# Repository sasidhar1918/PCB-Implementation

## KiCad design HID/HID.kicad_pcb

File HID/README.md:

# RP2040 Custom HID Device: Technical Implementation

## 🚀 Project Overview
This project is a high-performance Human Interface Device (HID) built on the **Raspberry Pi RP2040** microcontroller. Moving beyond simple breadboard prototypes, this implementation features a production-ready PCB designed to handle high-speed USB data signals with professional-grade integrity.

---

## 🛠️ My Implementation Approach

### 1. High-Speed Data Integrity
For the USB-C interface, I prioritized signal quality for the **D+ and D- differential pairs**:
* **Routing:** Minimal trace length to reduce latency and interference.
* **Isolation:** Kept data lines isolated from noisy power components.
* **Grounding:** Implemented a robust ground system to provide a stable reference and prevent data corruption.

### 2. Thermal & Noise Management (Via Stitching)
A key technical feature of this design is the strategic use of **GND Via Stitching**:
* **Copper Pours:** Large planes on both Top and Bottom layers to eliminate "floating islands."
* **EMI Shielding:** Manual via placement creates a "Faraday cage" effect to suppress electrical noise.
* **Thermal Dissipation:** Efficiently transfers heat from the RP2040 into the bottom copper plane.

### 3. Power Delivery Architecture
Designed to handle 5V input from the USB-C receptacle with a focus on stability:
* **Filtering:** series of decoupling capacitors to suppress high-frequency noise.
* **Proximity:** Components placed as close as possible to the RP2040 power pins to handle sudden current draws from the dual-core processor.

### 4. Design for Excellence (DfX)
The layout adheres to strict **Design Rule Checks (DRC)** for seamless manufacturing:
* **Soldering:** Clearances optimized for easy component assembly.
* **Legibility:** Silkscreen labels are positioned to avoid overlap with solder pads.
* **CNC Ready:** Precisely defined board edges for factory routing.

---

## 📊 Technical Specifications

| Feature | Specification |
| :--- | :--- |
| **Core** | RP2040 (Dual ARM Cortex-M0+ @ 133MHz) |
| **Interface** | USB 2.0 via USB-C |
| **PCB Topology** | 2-Layer FR-4, 1.6mm thickness |
| **Grounding** | Symmetrical Top/Bottom copper pours with via stitching |

---

## 📂 How to Use This Project
This repository contains the full design source. You can explore the implementation details within the **KiCad files**, where I have documented:
* Specific trace widths.
* Clearance constraints used to achieve a **zero-error DRC report**.

---
*Designed and implemented with a focus on signal integrity and professional PCB manufacturing standards.*

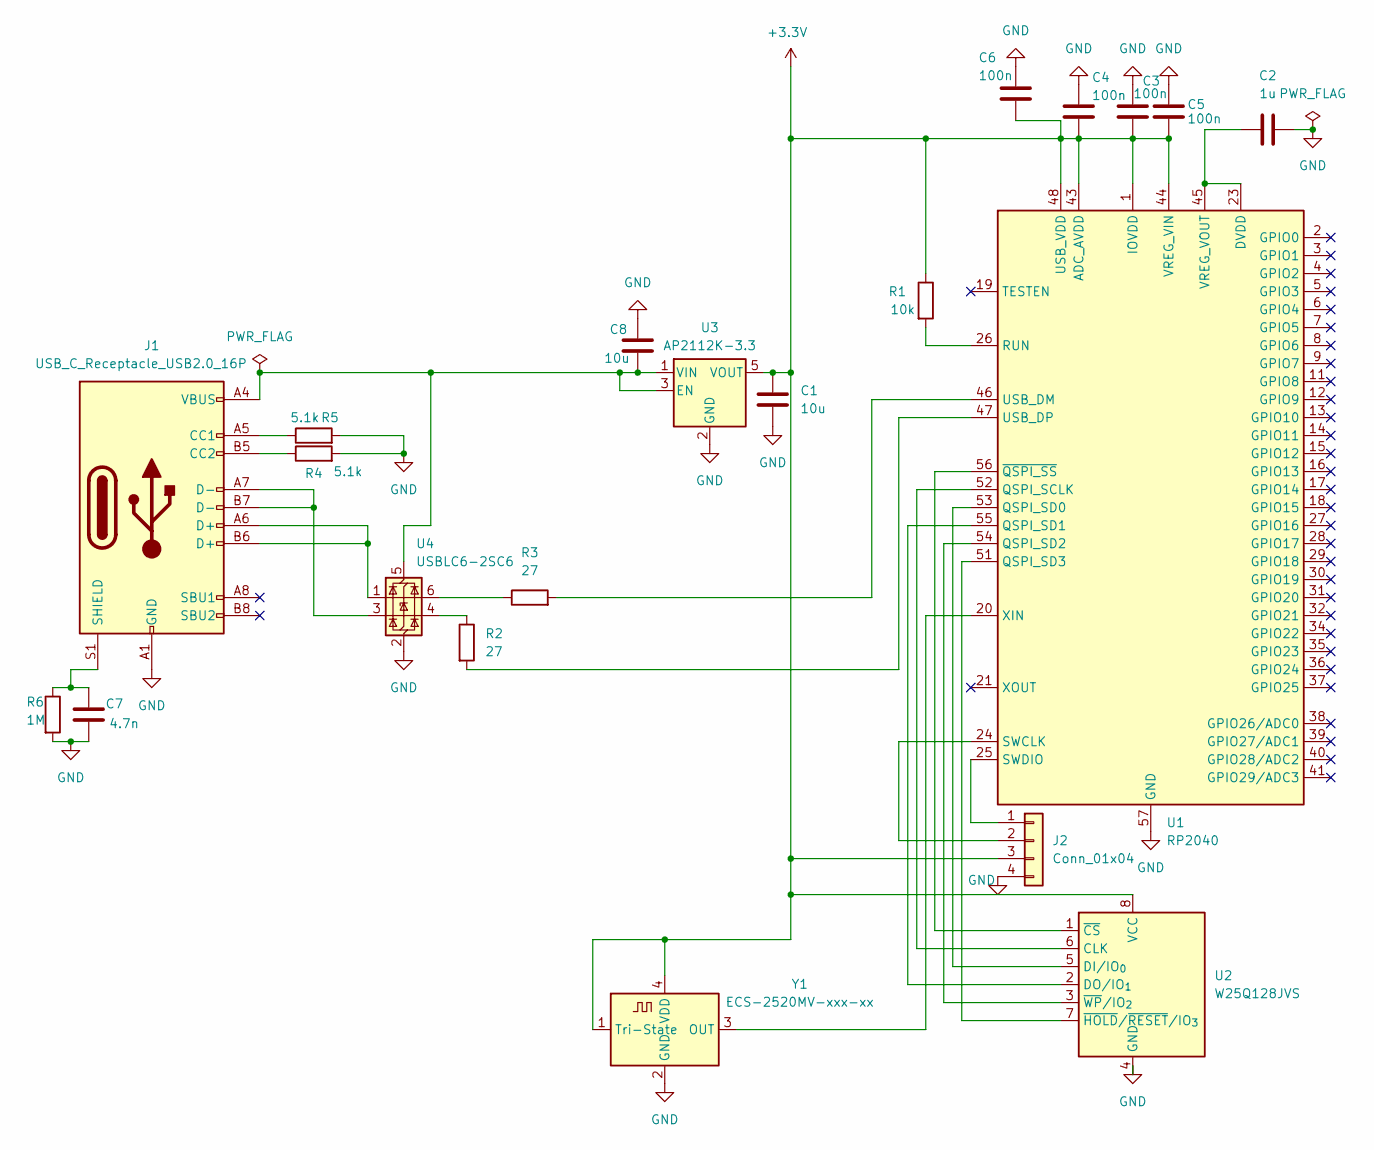
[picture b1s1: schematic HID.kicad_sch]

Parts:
C1, C8: 10u; C_0805_2012Metric_Pad1.18x1.45mm_HandSolder
C2: 1u; C_0805_2012Metric_Pad1.18x1.45mm_HandSolder
C3, C4, C5, C6: 100n; C_0805_2012Metric_Pad1.18x1.45mm_HandSolder
C7: 4.7n; C_0805_2012Metric_Pad1.18x1.45mm_HandSolder
J1: USB_C_Receptacle_USB2.0_16P; USB_C_Receptacle_GCT_USB4110
J2: Conn_01x04; PinHeader_1x04_P1.27mm_Vertical
R1: 10k; R_0805_2012Metric_Pad1.20x1.40mm_HandSolder
R2, R3: 27; R_0805_2012Metric_Pad1.20x1.40mm_HandSolder
R4, R5: 5.1k; R_0805_2012Metric_Pad1.20x1.40mm_HandSolder
R6: 1M; R_0805_2012Metric_Pad1.20x1.40mm_HandSolder
U1: RP2040; QFN-56-1EP_7x7mm_P0.4mm_EP3.2x3.2mm
U2: W25Q128JVS; SOIC-8_5.3x5.3mm_P1.27mm
U3: AP2112K-3.3; SOT-23-5
U4: USBLC6-2SC6; SOT-23-6
Y1: ECS-2520MV-xxx-xx; Oscillator_SMD_ECS_2520MV-xxx-xx-4Pin_2.5x2.0mm

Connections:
+3.3V: C1.1, C3.2, C4.2, C5.2, C6.2, J2.3, R1.1, U1.1 (IOVDD), U1.10 (IOVDD), U1.22 (IOVDD), U1.33 (IOVDD), U1.42 (IOVDD), U1.43 (ADC_AVDD), U1.44 (VREG_VIN), U1.48 (USB_VDD), U1.49 (IOVDD), U2.8 (VCC), U3.5 (VOUT), Y1.1 (Tri-State), Y1.4 (VDD)
GND: C1.2, C2.2, C3.1, C4.1, C5.1, C6.1, C7.2, C8.1, J1.A1 (GND), J1.A12 (GND), J1.B1 (GND), J1.B12 (GND), J2.4, R4.2, R5.2, R6.2, U1.57 (GND), U2.4 (GND), U3.2 (GND), U4.2 (GND), Y1.2 (GND)
unnamed: J1.A5 (CC1), R5.1
unnamed: J1.B5 (CC2), R4.1
unnamed: J1.A6 (D+), J1.B6 (D+), U4.1 (I/O1)
unnamed: J1.A7 (D-), J1.B7 (D-), U4.3 (I/O2)
unnamed: C7.1, J1.S1 (SHIELD), R6.1
unnamed: J2.1, U1.25 (SWDIO)
unnamed: J2.2, U1.24 (SWCLK)
unnamed: R2.1, U4.4 (I/O2)
unnamed: R3.1, U4.6 (I/O1)
unnamed: U1.52 (QSPI_SCLK), U2.6 (CLK)
unnamed: U1.53 (QSPI_SD0), U2.5 (DI/IO_{0})
unnamed: U1.55 (QSPI_SD1), U2.2 (DO/IO_{1})
unnamed: U1.54 (QSPI_SD2), U2.3 (~WP/IO_{2})
unnamed: U1.51 (QSPI_SD3), U2.7 (~HOLD/~RESET/IO_{3})
unnamed: R1.2, U1.26 (RUN)
unnamed: R3.2, U1.46 (USB_DM)
unnamed: R2.2, U1.47 (USB_DP)
unnamed: C2.1, U1.23 (DVDD), U1.45 (VREG_VOUT), U1.50 (DVDD)
unnamed: U1.20 (XIN), Y1.3 (OUT)
unnamed: U1.56 (~QSPI_SS), U2.1 (~CS)
unnamed: C8.2, J1.A4 (VBUS), J1.A9 (VBUS), J1.B4 (VBUS), J1.B9 (VBUS), U3.1 (VIN), U3.3 (EN), U4.5 (VBUS)

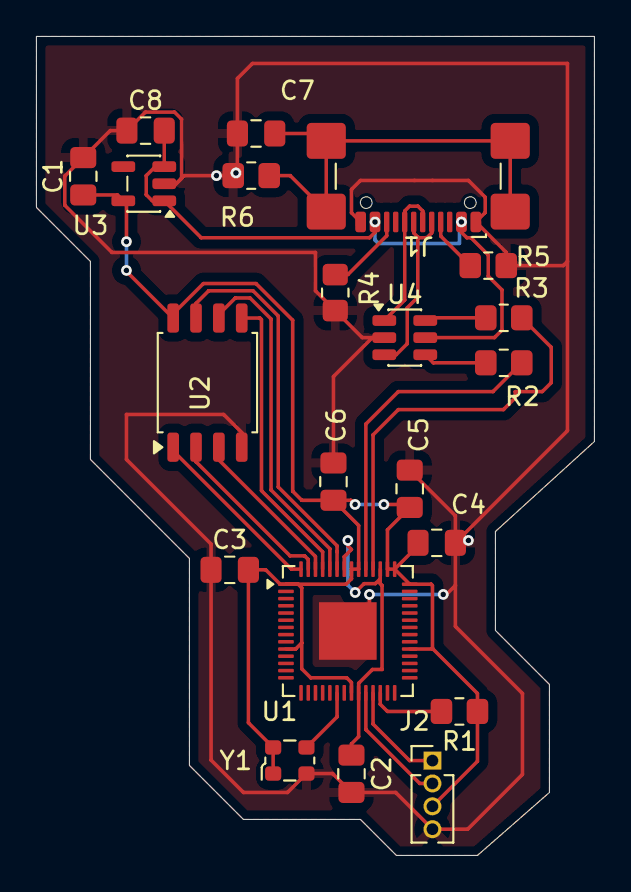
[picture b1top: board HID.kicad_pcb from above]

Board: 2 copper layers, 31.0 x 45.5 mm, 21 parts (0 on the bottom side), 23 nets.

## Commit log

2026-03-02 PCB implementation of HID
